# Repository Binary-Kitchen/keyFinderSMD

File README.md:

# KeyfinderSMD

A simple small key-finder for your keys. If you whistle the key-finder beeps.

## Bill of Material
TBD

## Manual
TBD

## Copyright and Authorship
- PCB-Layout: [CC-BY-SA 3.0](https://creativecommons.org/licenses/by-sa/4.0/) - [Thomas Schmid and Timo Schindler](https://www.binary-kitchen.de)
- Manual (TeX): [LPPL](https://www.latex-project.org/lppl.txt) - [Marei Peischl](https://peitex.de)
- Manual (pdf): [CC-BY-SA 4.0](https://creativecommons.org/licenses/by-sa/4.0/) - [Binary Kitchen e.V.](https://www.binary-kitchen.de)

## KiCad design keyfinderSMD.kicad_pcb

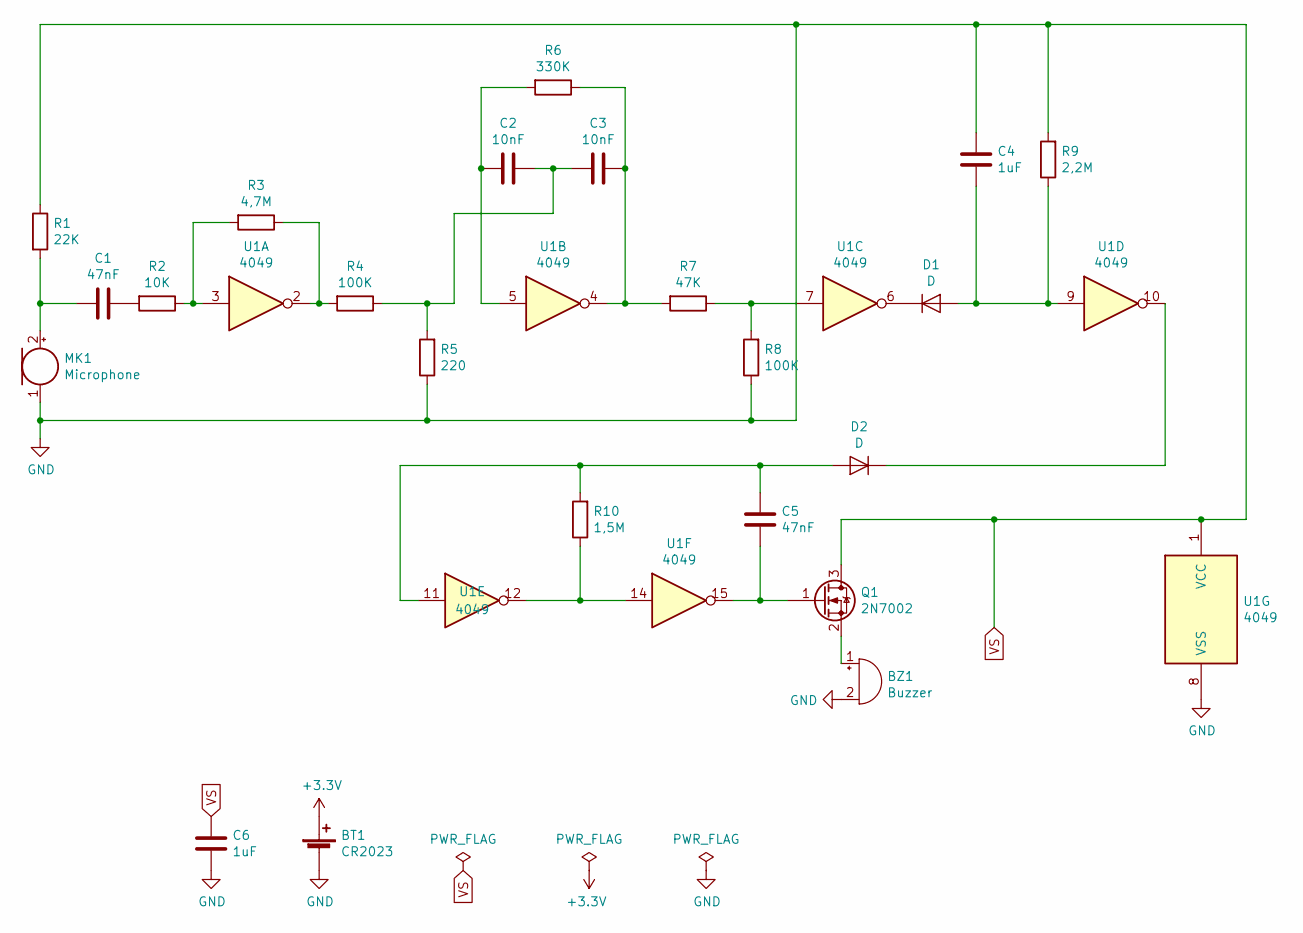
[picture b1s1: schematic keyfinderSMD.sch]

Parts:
BT1: CR2023; BatteryHolder_Keystone_1060_1x2032
BZ1: Buzzer; Buzzer_12x9.5RM7.6
C1, C5: 47nF; C_0805_2012Metric_Pad1.15x1.40mm_HandSolder
C2, C3: 10nF; C_0805_2012Metric_Pad1.15x1.40mm_HandSolder
C4, C6: 1uF; C_0805_2012Metric_Pad1.15x1.40mm_HandSolder
D1, D2: D; D_0805_2012Metric_Pad1.15x1.40mm_HandSolder
MK1: Microphone; MicrophoneDIP
Q1: 2N7002; SOT-23
R1: 22K; R_0805_2012Metric_Pad1.15x1.40mm_HandSolder
R2: 10K; R_0805_2012Metric_Pad1.15x1.40mm_HandSolder
R3: 4,7M; R_0805_2012Metric_Pad1.15x1.40mm_HandSolder
R4, R8: 100K; R_0805_2012Metric_Pad1.15x1.40mm_HandSolder
R5: 220; R_0805_2012Metric_Pad1.15x1.40mm_HandSolder
R6: 330K; R_0805_2012Metric_Pad1.15x1.40mm_HandSolder
R7: 47K; R_0805_2012Metric_Pad1.15x1.40mm_HandSolder
R9: 2,2M; R_0805_2012Metric_Pad1.15x1.40mm_HandSolder
R10: 1,5M; R_0805_2012Metric_Pad1.15x1.40mm_HandSolder
U1: 4049; SOIC-16_3.9x9.9mm_P1.27mm

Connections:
+3V3: BT1.1 (+)
unnamed: BZ1.1 (-), Q1.2 (S)
unnamed: C1.1, R2.2
unnamed: C1.2, MK1.2 (+), R1.2
unnamed: C2.1, C3.2, R4.1, R5.2
unnamed: C2.2, R6.2, U1.5
unnamed: C3.1, R6.1, R7.2, U1.4
unnamed: C4.1, D1.2 (A), R9.1, U1.9
unnamed: C5.1, Q1.1 (G), U1.15
unnamed: C5.2, D2.2 (A), R10.2, U1.11
unnamed: D1.1 (K), U1.6
unnamed: D2.1 (K), U1.10
unnamed: R2.1, R3.2, U1.3
unnamed: R3.1, R4.2, U1.2
unnamed: R7.1, R8.2, U1.7
unnamed: R10.1, U1.12, U1.14
VS: BT1.2 (-), BZ1.2 (+), C4.2, C6.1, C6.2, MK1.1 (-), Q1.3 (D), R1.1, R5.1, R8.1, R9.2, U1.1 (VCC), U1.8 (VSS)

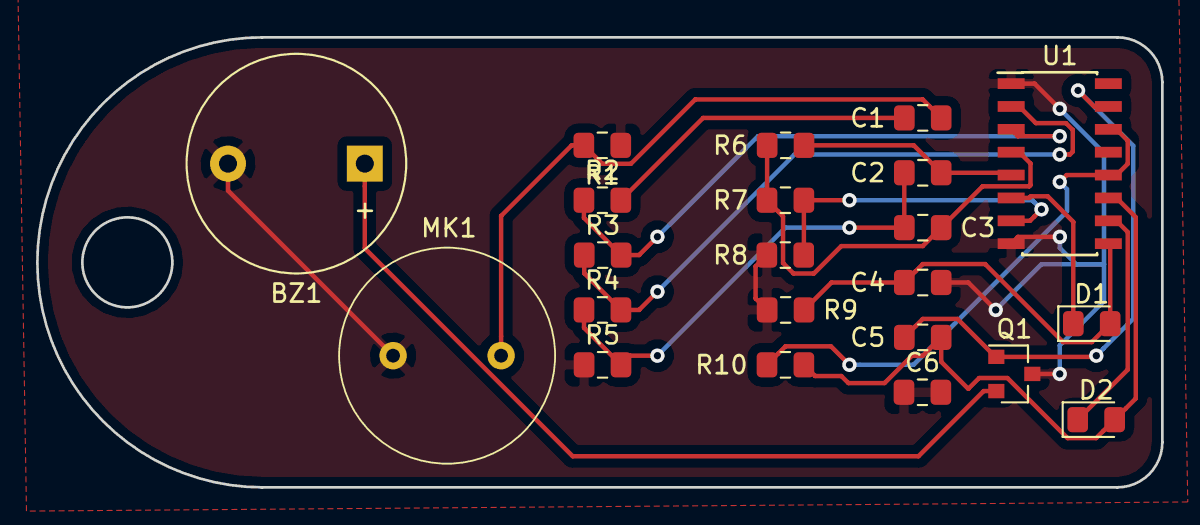
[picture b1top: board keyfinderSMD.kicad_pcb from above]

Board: 2 copper layers, 62.5 x 25.0 mm, 23 parts (1 on the bottom side), 16 nets.

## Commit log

2018-12-05 added .gitignore
2018-12-05 added simple readme
2018-12-05 added licence file
2018-12-05 fixed typos
2018-12-05 fixed syntax error
2018-12-05 added first draft
